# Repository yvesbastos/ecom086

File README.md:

# ecom086
Assignments for ECOM086 (Printed Circuits) Class

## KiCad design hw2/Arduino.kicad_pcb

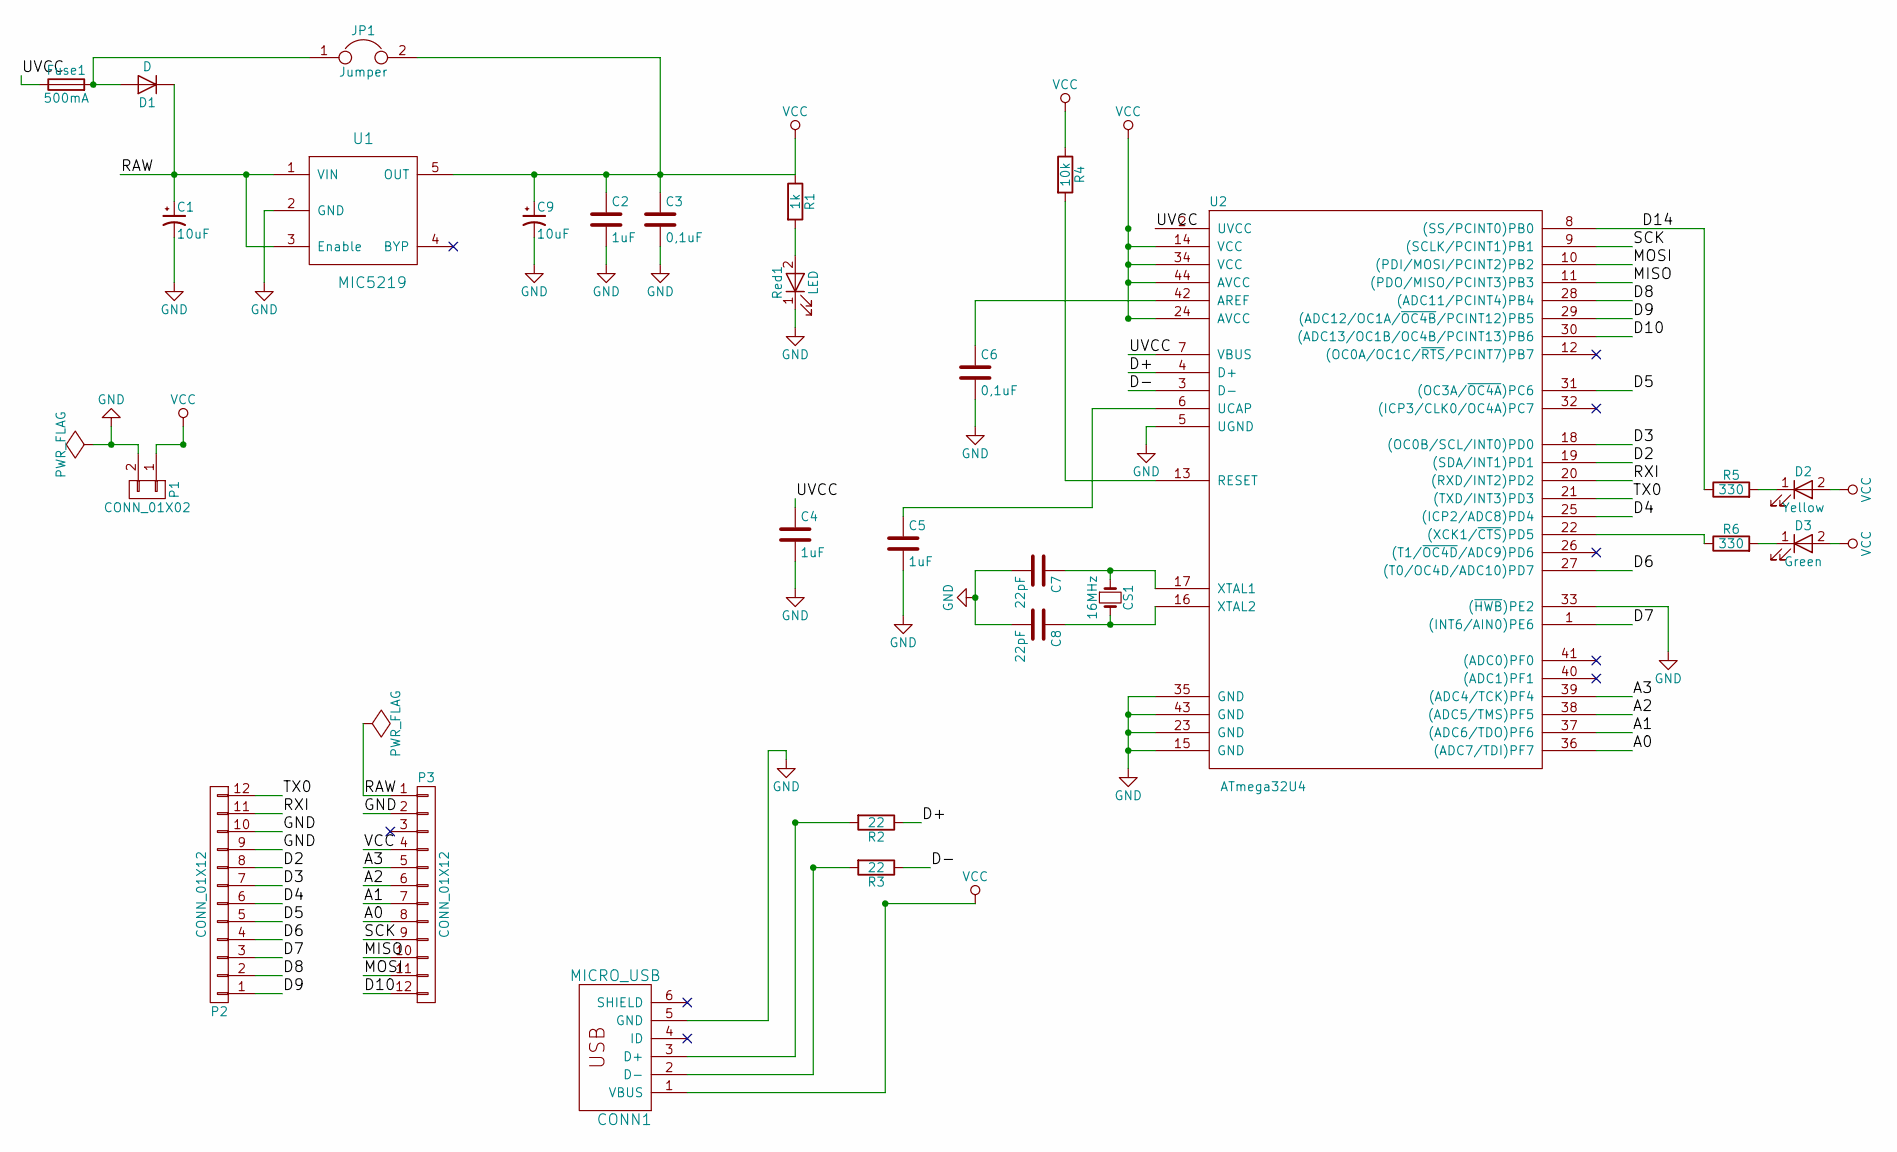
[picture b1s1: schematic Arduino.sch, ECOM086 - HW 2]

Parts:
C1, C9: 10uF; CP_Elec_3x5.3
C2, C4, C5: 1uF; C_0805
C3, C6: 0,1uF; C_0805
C7, C8: 22pF; C_0805
CONN1: MICRO_USB; USB_Micro-B
CS1: 16MHz; Crystal_AT310_d3.0mm_l10.0mm_Horizontal
D1: D; D_0805
D2: Yellow; LED_0805
D3: Green; LED_0805
Fuse1: 500mA; Fuse_SMD1206_HandSoldering
JP1: Jumper; Pin_Header_Straight_1x02_Pitch1.27mm
P1: CONN_01X02; Socket_Strip_Angled_1x02_Pitch2.00mm
P2, P3: CONN_01X12; Pin_Header_Straight_1x12_Pitch1.27mm
R1: 1k; R_0805
R2, R3: 22; R_0805
R4: 10k; R_0805
R5, R6: 330; R_0805
Red1: LED; LED_0805
U1: MIC5219; SOT-23
U2: ATmega32U4; LQFP-44_10x10mm_Pitch0.8mm

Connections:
/A0: P3.8, U2.36 ((ADC7/TDI)PF7)
/A1: P3.7, U2.37 ((ADC6/TDO)PF6)
/A2: P3.6, U2.38 ((ADC5/TMS)PF5)
/A3: P3.5, U2.39 ((ADC4/TCK)PF4)
/D2: P2.8, U2.19 ((SDA/INT1)PD1)
/D3: P2.7, U2.18 ((OC0B/SCL/INT0)PD0)
/D4: P2.6, U2.25 ((ICP2/ADC8)PD4)
/D5: P2.5, U2.31 ((OC3A/~OC4A~)PC6)
/D6: P2.4, U2.27 ((T0/OC4D/ADC10)PD7)
/D7: P2.3, U2.1 ((INT6/AIN0)PE6)
/D8: P2.2, U2.28 ((ADC11/PCINT4)PB4)
/D9: P2.1, U2.29 ((ADC12/OC1A/~OC4B~/PCINT12)PB5)
/D10: P3.12, U2.30 ((ADC13/OC1B/OC4B/PCINT13)PB6)
/D14: R5.1, U2.8 ((SS/PCINT0)PB0)
/D+: R2.1, U2.4 (D+)
/D-: R3.1, U2.3 (D-)
/MISO: P3.10, U2.11 ((PDO/MISO/PCINT3)PB3)
/MOSI: P3.11, U2.10 ((PDI/MOSI/PCINT2)PB2)
/RAW: C1.1, D1.1 (K), P3.1, U1.1 (VIN), U1.3 (Enable)
/RXI: P2.11, U2.20 ((RXD/INT2)PD2)
/SCK: P3.9, U2.9 ((SCLK/PCINT1)PB1)
/TX0: P2.12, U2.21 ((TXD/INT3)PD3)
/UVCC: C4.1, Fuse1.1, U2.2 (UVCC), U2.7 (VBUS)
GND: C1.2, C2.2, C3.2, C4.2, C5.2, C6.2, C7.2, C8.2, C9.2, CONN1.5 (GND), P1.2, P2.9, P2.10, P3.2, Red1.1 (K), U1.2 (GND), U2.5 (UGND), U2.15 (GND), U2.23 (GND), U2.33 ((~HWB~)PE2), U2.35 (GND), U2.43 (GND); also elsewhere on the board
unnamed: C5.1, U2.6 (UCAP)
unnamed: C6.1, U2.42 (AREF)
unnamed: C7.1, CS1.1, U2.17 (XTAL1)
unnamed: C8.1, CS1.2, U2.16 (XTAL2)
unnamed: D1.2 (A), Fuse1.2, JP1.1
unnamed: D2.1 (K), R5.2
unnamed: D3.1 (K), R6.2
unnamed 32: CONN1.2 (D-), R3.2; also elsewhere on the board
unnamed 33: CONN1.3 (D+), R2.2; also elsewhere on the board
unnamed: R1.2, Red1.2 (A)
unnamed: R4.2, U2.13 (RESET)
unnamed: R6.1, U2.22 ((XCK1/~CTS~)PD5)
VCC: C2.1, C3.1, C9.1, CONN1.1 (VBUS), D2.2 (A), D3.2 (A), JP1.2, P1.1, P3.4, R1.1, R4.1, U1.5 (OUT), U2.14 (VCC), U2.24 (AVCC), U2.34 (VCC), U2.44 (AVCC); also elsewhere on the board

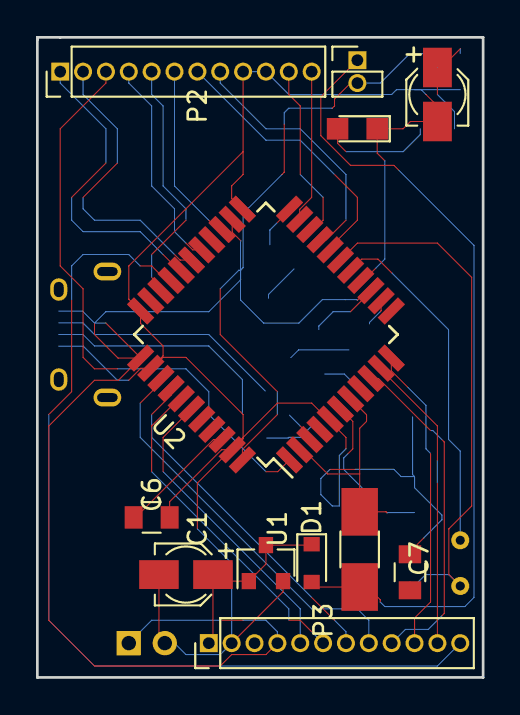
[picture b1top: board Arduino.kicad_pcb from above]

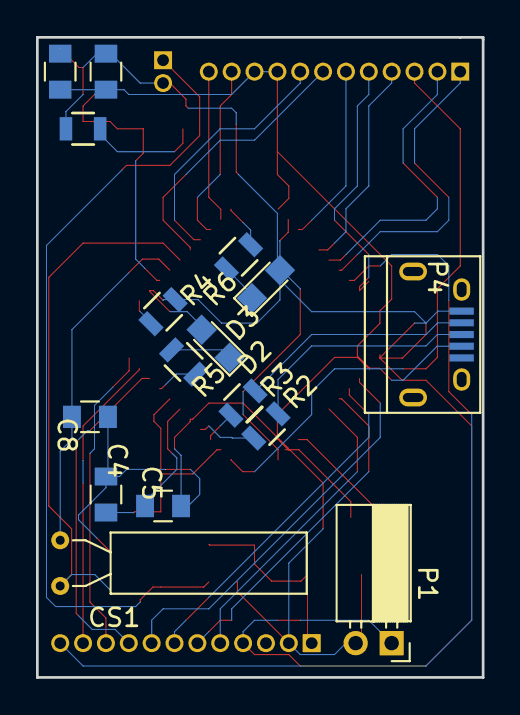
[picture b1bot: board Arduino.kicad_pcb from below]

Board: 2 copper layers, 24.8 x 35.6 mm, 28 parts (16 on the bottom side), 37 nets.

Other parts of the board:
P4: USB-A-PCB; USB_Micro-B

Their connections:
GND: P4.4; also elsewhere on the board
unnamed 32: P4.2; also elsewhere on the board
unnamed 33: P4.3; also elsewhere on the board
VCC: P4.1; also elsewhere on the board

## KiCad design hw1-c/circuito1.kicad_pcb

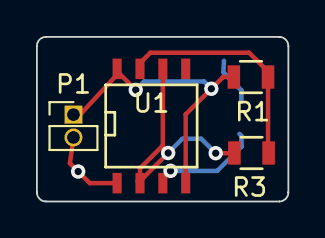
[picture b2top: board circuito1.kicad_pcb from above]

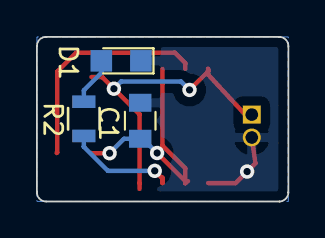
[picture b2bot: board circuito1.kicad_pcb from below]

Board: 2 copper layers, 14.0 x 9.1 mm, 7 parts (3 on the bottom side), 6 nets.

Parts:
C1: C; C_0805
D1: LED; LED_0805
P1: CONN_01X02; Socket_Strip_Straight_1x02_Pitch1.27mm
R1, R2: 1K; R_0805
R3: 470K; R_0805
U1: LM555N; SOIC-8-N

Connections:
GND: C1.1, D1.1, P1.2, U1.1
unnamed: C1.2, R3.2, U1.2, U1.6
unnamed: D1.2, R2.1
unnamed: R1.1, R3.1, U1.7
unnamed: R2.2, U1.3
VCC: P1.1, R1.2, U1.4, U1.8

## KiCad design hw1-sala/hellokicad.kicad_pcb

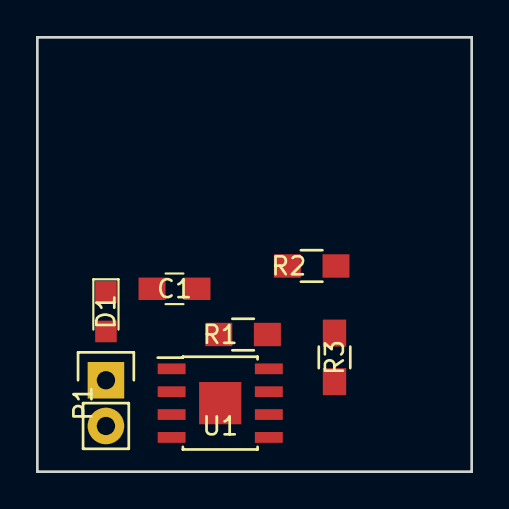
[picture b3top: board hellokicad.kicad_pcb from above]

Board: 2 copper layers, 24.1 x 24.1 mm, 7 parts (0 on the bottom side), 6 nets, no tracks yet.

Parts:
C1: C; C_0805_HandSoldering
D1: LED; LED_0805
P1: CONN_01X02; Socket_Strip_Straight_1x02
R1: R; R_0805_HandSoldering
R2: 470K; R_0805_HandSoldering
R3: 1K; R_0805_HandSoldering
U1: LM555N; SOIC-8-1EP_3.9x4.9mm_Pitch1.27mm

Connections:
/A: C1.2, R2.1, U1.2, U1.6
GND: C1.1, D1.1, P1.1, U1.1
unnamed: D1.2, R1.1
unnamed: R1.2, U1.3
unnamed: R2.2, R3.1, U1.7
VCC: P1.2, R3.2, U1.4, U1.8

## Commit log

2017-02-14 Schematic almost complete
2017-02-15 Schema finalized
2017-02-15 Schema footprint association almost finalized
2017-02-17 Corrections in schema; pcb layout implementation initialized
2017-02-17 Initial changes
2017-02-17 Main elements repositioned
2017-02-17 Advances in pcblayout
2017-02-18 hw1 files added
2017-02-18 Tracks initialized
2017-02-19 Routing finalized
2017-02-19 USB footprint correctd; routing updated; report updated
2017-02-19 hw1 files reorganized
